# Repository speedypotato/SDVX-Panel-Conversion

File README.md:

# SDVX-Panel-Conversion
Turn an arcade Sound Voltex panel into a controller.

Requires a 1x2ft laser cutter, a 3d printer, and an assortment of m3 and m4 nuts and bolts.  And rubber feet.  And some more stuff.

issues:  
- arduino holes didn't exactly line up, i just screwed in 2 screws diagonally and called it a day
- the m3x20 screws may fall out.  the corner brackets seem to do a good enough job,  can super glue m3 washers to make the m3x20 screws stay.

Note: PCB folder contains a side led rgb pcb which i was originally going to use, but the pcba turned out too expensive so I have went with the 3d printed mount instead

requires:  
- 2 1/4" 1x2ft plywood panels - mine came out to be 5.5mm..so ymmv.  Laser cut with box_dxf, units are mm
- 3d printed parts: 4 corner_bracket, 2 back_mount, 2 front_mount, 1 usb_mount, 1 arduino_leonaro_mount, 1 led_3dp, and 1 led_3dp but print mirrored
- 3m mounting tape for arduino and led sides
- m3x6 arduino
- m3x16 corner brackets
- m4x12 panel to box mount
- m3 nuts
- m4 nuts
- m3 washers
- m4 washers
- m4xsomething nuts to mount arcade panel to box
- m4 screwable rubber feet.  I got these https://www.mcmaster.com/8884T21
- top screws.  got them from a friend, they look like m4 low/slim profile of some sort.  m4x16 or something.
- ws2812b strip - i got 1m of 144leds/m because why not.

Assembly:  
- Note: I recommend doing a washer wherever a screw head touches wood or a 3d print.
- screw together box with corner pieces
- glue usb c - micro b extender into the usb holder
- screw in usb holder
- screw in front and back 3d printed mounts to box, don't forget to add nuts to all 3 points
- screw in panel
- mount arduino to plastic holder, apply 3m tape to holder.
- create wiring harness or just use dupont breadboard extenders and plug it directly into the connector using the wiring guide.  I recommend grouping all the - and COM to ground, except L/R Pot -, which get their own dedicated wire to ground
- don't forget to wire up ws2812b, needs to tap into 5v and gnd of the harness and each side has its own dedicated data line.  Cut to length, for mine i did 31 leds per side.
- assuming you've wired up arduino, plug in the micro usb adapter, peel off other side of 3m tape and mount it inside.  for me, i did it in the top left corner(looking at the top of the panel)
- string ws2812b strips through the half circle gaps to the outside of the box.
- apply mounting tape to edges of led_3dp part, then stick ws2812b strip to the mount.  Peel mounting tape and apply to panel.  Repeat for other side.
- mount feet to the bottom panel
- screw in the bottom panel

Setup https://github.com/veroxzik/arduino-konami-spoof (C:\Program Files (x86)\Arduino\hardware for me) and flash SkogaVoltex.  Might need to add arduino joystick library(just google it and import the zip).  Fastled, bounce2, and responsiveanalogread libraries can be installed through tools -> manage libraries.

This work is licensed under a Creative Commons Attribution-NonCommercial-ShareAlike 4.0 International License.

My build, including extras:  
dupont	7.3  
ws2812b	8.26  
panel	63.51  
shipping	69.5  
arduino	14.99  
usb c to micro b	1.915  
wood	8.47  
screws	15.89  
feet	3.18  
3d prints	5  
jst	0  
wire	1  
torque limiter	44  
yuan leds	11.01  
usb c cable	1  
knobs	19.98 
3m tape 5 

Total: 280.005

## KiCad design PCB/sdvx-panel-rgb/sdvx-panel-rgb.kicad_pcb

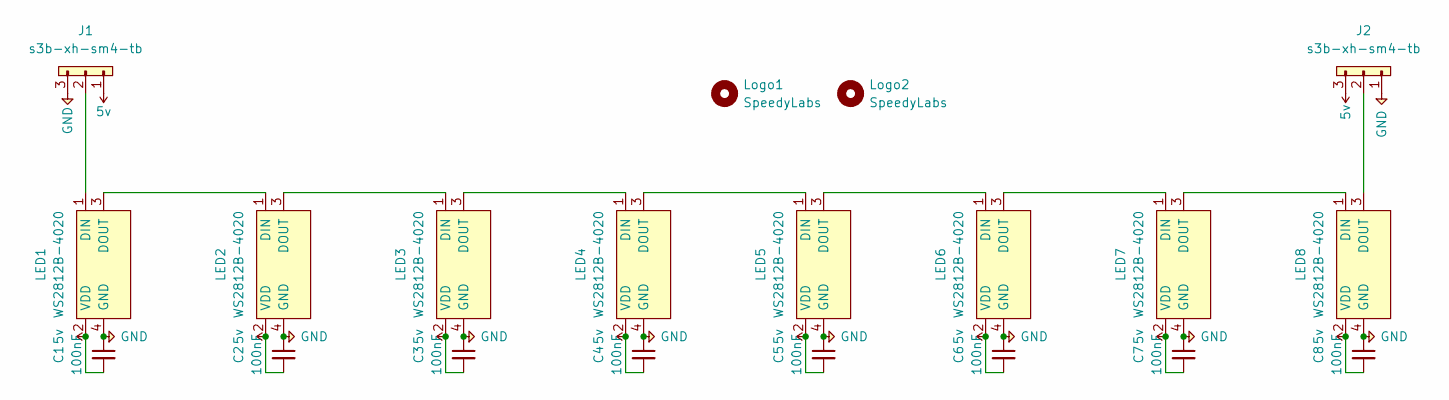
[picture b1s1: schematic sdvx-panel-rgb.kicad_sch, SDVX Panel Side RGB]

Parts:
C1, C2, C3, C4, C5, C6, C7, C8: 100nF; C_0603_1608Metric_Pad1.08x0.95mm_HandSolder; LCSC C1525
J1, J2: s3b-xh-sm4-tb; S3B-XH-SM4-TB; LCSC C161860
LED1, LED2, LED3, LED4, LED5, LED6, LED7, LED8: WS2812B-4020; LCSC C965557
Logo1, Logo2: SpeedyLabs; logo_small

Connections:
5v: C1.2, C2.2, C3.2, C4.2, C5.2, C6.2, C7.2, C8.2, J1.1, J2.3, LED1.2 (VDD), LED2.2 (VDD), LED3.2 (VDD), LED4.2 (VDD), LED5.2 (VDD), LED6.2 (VDD), LED7.2 (VDD), LED8.2 (VDD)
GND: C1.1, C2.1, C3.1, C4.1, C5.1, C6.1, C7.1, C8.1, J1.3, J2.1, LED1.4 (GND), LED2.4 (GND), LED3.4 (GND), LED4.4 (GND), LED5.4 (GND), LED6.4 (GND), LED7.4 (GND), LED8.4 (GND)
unnamed: J1.2, LED1.1 (DIN)
unnamed: LED1.3 (DOUT), LED2.1 (DIN)
unnamed: LED2.3 (DOUT), LED3.1 (DIN)
unnamed: LED3.3 (DOUT), LED4.1 (DIN)
unnamed: LED4.3 (DOUT), LED5.1 (DIN)
unnamed: LED5.3 (DOUT), LED6.1 (DIN)
unnamed: LED6.3 (DOUT), LED7.1 (DIN)
unnamed: LED7.3 (DOUT), LED8.1 (DIN)
unnamed: J2.2, LED8.3 (DOUT)

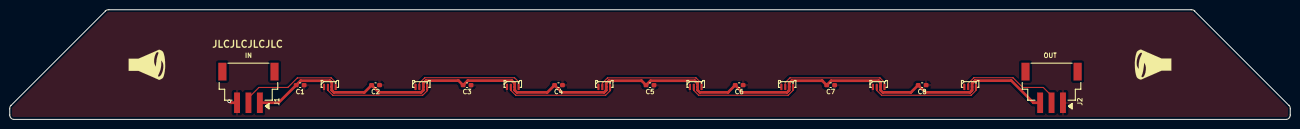
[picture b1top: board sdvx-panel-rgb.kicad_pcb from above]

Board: 2 copper layers, 280.0 x 24.0 mm, 20 parts (0 on the bottom side), 11 nets.

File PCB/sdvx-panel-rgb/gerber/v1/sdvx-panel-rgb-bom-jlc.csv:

Comment,Designator,Footprint,LCSC
100nF,"C1,C2,C3,C4,C5,C6,C7,C8",Capacitor_SMD:C_0603_1608Metric_Pad1.08x0.95mm_HandSolder,C1525
s3b-xh-sm4-tb,"J1,J2",user:S3B-XH-SM4-TB,C161860
WS2812B-4020,"LED1,LED2,LED3,LED4,LED5,LED6,LED7,LED8",agg:WS2812B-4020,C965557

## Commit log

2022-08-20 Initial upload, v1 RGB PCB
2022-09-24 v1, everything but rgb strip support
2022-09-24 added internal corner brackets in case edge ones aren't good enough
2022-09-26 added screws, wiring, and firmware (thanks skogaby)
2022-09-27 docs and final firmware
2022-10-09 Finished build
2023-04-07 Removed side screw points
